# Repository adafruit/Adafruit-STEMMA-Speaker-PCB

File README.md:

## Adafruit STEMMA Speaker Plug and Play Audio Amplifier PCB

<a href="http://www.adafruit.com/products/3885"><br/>
Click here to purchase one from the Adafruit shop</a>

PCB files for the Adafruit STEMMA Speaker Plug and Play Audio Amplifier. 

Format is EagleCAD schematic and board layout
* https://www.adafruit.com/product/3885

### Description

Hey, have you heard the good news? With Adafruit STEMMA boards you can easily and safely plug sensors and devices together, like this Adafruit STEMMA Speaker - Plug and Play Audio Amplifier. Like the name implies, it's got a class D audio amplifier on board, and our favorite little 1 Watt 8 ohm speaker.

Connecting it up is easy - you only need ground, 3 to 5V power, and audio signal. The audio signal does not need to be AC coupled, we do that for you, and can range up to the power pin voltage (3 or 5V peak-to-peak). You can use either the 3-pin JST socket or the alligator/sew-pads for this slim and portable package. The sound quality is good enough for music, tones, speech, whatever you like and volume can be adjusted with a small screwdriver.

For use with a CircuitPlayground or micro:bit, this JST to alligator-clip cable works best. Red is power, ground is black and signal is white.

For use with a breadboard, try this JST to male/plug-header. (We also have a socket-header cable if you want)

### License

Adafruit invests time and resources providing this open source design, please support Adafruit and open-source hardware by purchasing products from [Adafruit](https://www.adafruit.com)!

Designed by Limor Fried/Ladyada for Adafruit Industries.

Creative Commons Attribution/Share-Alike, all text above must be included in any redistribution. 
See license.txt for additional details.

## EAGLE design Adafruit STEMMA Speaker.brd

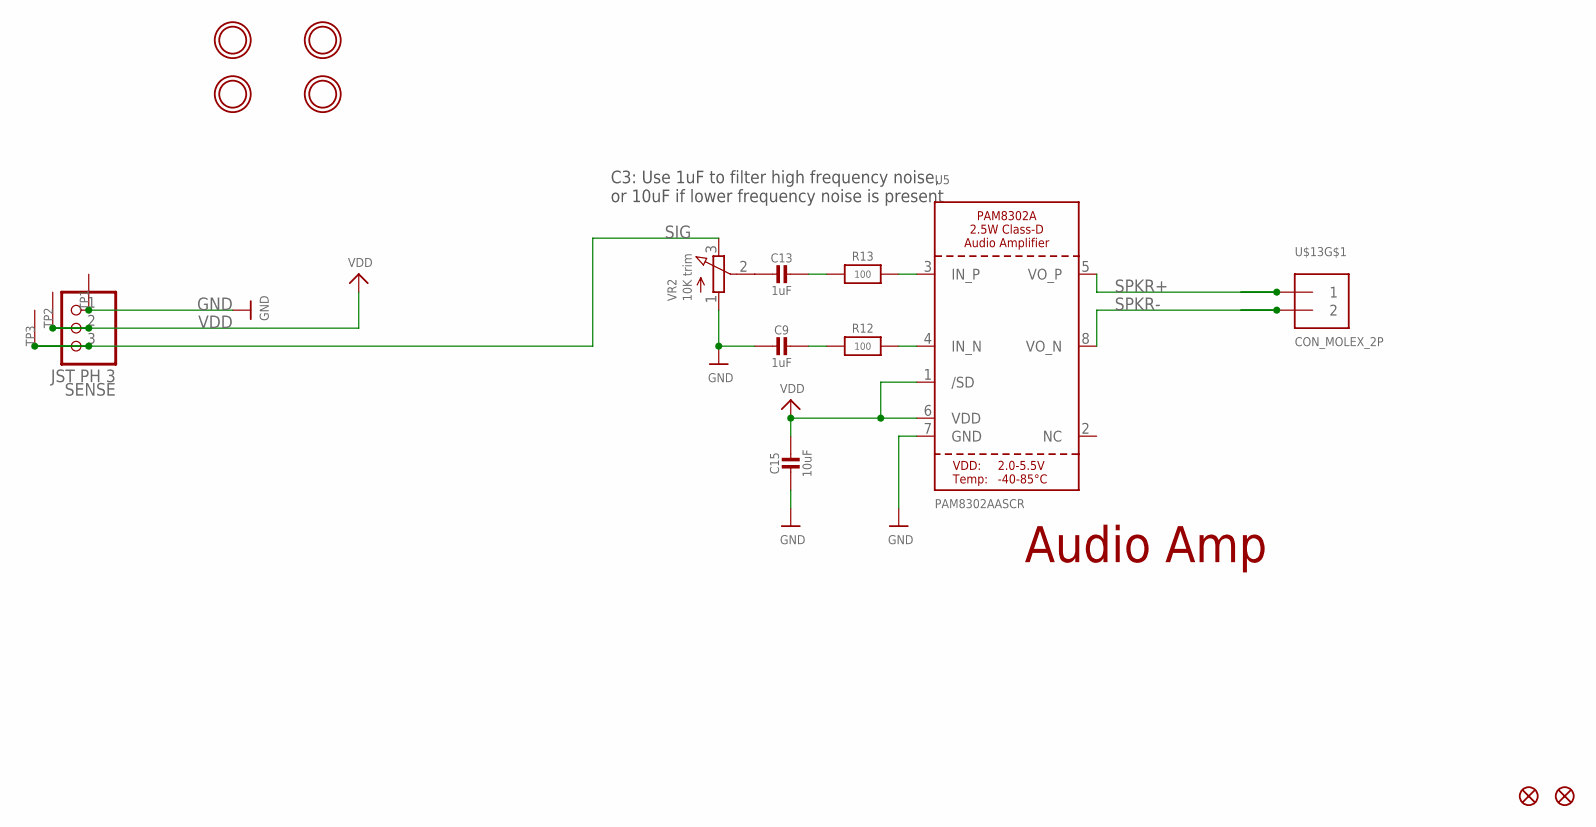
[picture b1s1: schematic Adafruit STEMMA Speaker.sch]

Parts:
C9, C13: 1uF; 0603-NO
C15: 10uF; 0805-NO
FID1, FID2: FIDUCIAL_1MM
R12, R13: 100; 0603-NO
SENSE: JST PH 3; JSTPH3
TP1, TP2, TP3: SEWTAPPCB_ALLIGATOR; PCB_ALLI
U5: PAM8302AASCR; MSOP8_0.65MM
U$9, U$10, U$11, U$12: MOUNTINGHOLE2.0; MOUNTINGHOLE_2.0_PLATED
U$13: CON_MOLEX_2P; 53398-0271
VR2: 10K trim; TRIMPOT_BOURNS_3303W

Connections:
GND: C9.2, C15.2, SENSE.1, TP1.P$1, U5.7 (GND), VR2.1 (A)
unnamed: R12.2, U5.4 (IN_N)
unnamed: R13.2, U5.3 (IN_P)
unnamed: C9.1, R12.1
unnamed: C13.1, R13.1
unnamed: C13.2, VR2.2 (S)
SIG: SENSE.3, TP3.P$1, VR2.3 (E)
SPKR+: U5.5 (VO_P), U$13.1
SPKR-: U5.8 (VO_N), U$13.2
VDD: C15.1, SENSE.2, TP2.P$1, U5.1 (/SD), U5.6 (VDD)

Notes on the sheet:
C3: Use 1uF to filter high frequency noise, or 10uF if lower frequency noise is present
Audio Amp

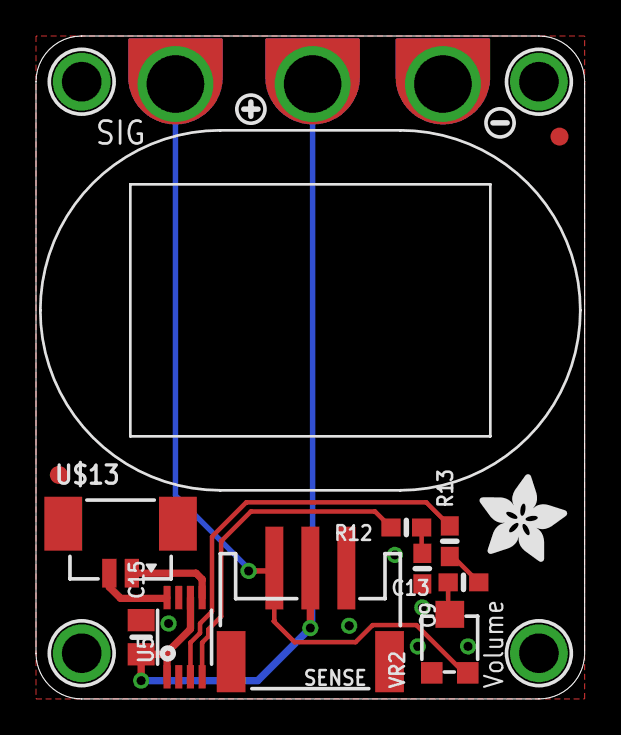
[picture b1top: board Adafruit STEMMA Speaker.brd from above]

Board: 2 copper layers, 30.5 x 36.8 mm, 23 parts (1 on the bottom side), 10 nets.

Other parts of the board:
U$1: SPEAKER_OVAL8OHM
U$3: ADAFRUIT_5MM
U$4: STEMMA_SPEAKER
U$5: SYMBOL_MINUS
U$6: SYMBOL_PLUS

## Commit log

2019-10-03 Adding board files.

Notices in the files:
parts and their libraries:
microbuilder: This work is placed in the public domain, and may be freely used for commercial and non-commercial work with the following conditions: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
